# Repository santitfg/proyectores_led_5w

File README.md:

# redo
en el 74hc595 el pin 10 (rst ) si o si a vcc
y el pin 13 output enable va a gng si o si 

### Conector 1 — entrada de datos serie (SER)

Chip: 74HC595 (registro de desplazamiento serie-in / paralelo-out). Molex 5 pines.

| Pin | Color | Señal | GPIO ESP32 | GPIO ESP32-S3 | Descripción |
|-----|-------|-------|------------|---------------|-------------|
| 1   | ⚫ Negro  | GND   | —          | —             | Tierra |
| 2   | ⚪ Blanco | SRCLK / CP | `gpio23`   | `gpio18`      | Shift Clock (SH_CP, pin 11) / SPI2 SCLK |
| 3   | 🟢 Verde  | RCLK / PL | `gpio22`   | `gpio10`      | Register Clock / Latch (ST_CP, pin 12) |
| 4   | 🩶 Gris   | SER  / DS | `gpio2`    | `gpio4`       | Serial data in (DS, pin 14) / SPI2 MOSI |
| 5   | 🔴 Rojo   | VCC   | —          | —             | Alimentación |

### Conector 2 — salida en cascada (Q7)

Conector para encadenar el `SER` (pin 14) del siguiente 74HC595 a la salida en cascada `Q7'` (pin 9) de este.

| Pin | Color | Señal | GPIO ESP32 | GPIO ESP32-S3 | Descripción |
|-----|-------|-------|------------|---------------|-------------|
| 1   | ⚫ Negro  | GND   | —          | —             | Tierra |
| 2   | ⚪ Blanco | SRCLK  / CP| `gpio23`   | `gpio18`      | Shift Clock (SH_CP, pin 11) / SPI2 SCLK |
| 3   | 🟢 Verde  | RCLK  / PL | `gpio22`   | `gpio10`      | Register Clock / Latch (ST_CP, pin 12) |
| 4   | 🩶 Gris   | Q7   | `gpio35`   | `gpio5`       | Salida en cascada (Q7', pin 9) hacia el `SER` del siguiente 74HC595 |
| 5   | 🔴 Rojo   | VCC   | —          | —             | Alimentación |

estoy controlando con el 74hc595 la matriz desde las siguientes filas y columnas:
Q0 ... Q3 se conectan a los 2n2222 controlanto el gate de IRF9630
Q4 ... Q7 se conectan directo al gate IRLZ44N

# revision de laburo

PCB

IRF9630 high side y esta a up down en gate
IRLZ44N	low side y esta a pull down en gate

————

revision en protoboard 5v y señales activas de irlz44n y 2n2222 a 3.3:
IRLZ44N
gate ( pin 1) 10k a pull Down 1k a señal (vcc activa el paso de corriente)
drain ( pin 2) a gnd-terminal
source (pin 3) a GND

IRF9630
gate ( pin 1) 10k a pull up 1k a señal (gnd activa el paso de corriente)(2n2222)
drain ( pin 2) a Vout-terminal
source (pin 3) a VIN

2n2222 ( funcionamiento real es emisor a gnd y colector lado vcc)
emisor (pin 1) a GND
base (pin 2) señal ic ( via 1k Resi)
colector (pin 3) ( señal hacia irf9630 via 1k resi) vcc activa el paso de corriente)x

TODO: arreglar kicad corrigiendo los elementos mencionados (inverti pista VIN x Vout-terminal)

Fallas en el circuito funciona la mitad de puntos en modo damero
O X O X
X O X O 
O X O X
X O X O

Nomenclar correstamente las columnas y filas 
pero los v y gnd en los mismos no todos fallan de la misma manera
1: 2: 3: 4: 

Filas
q0 (pin 15) : IRF9630 1
q1 (pin 1) : IRF9630 2
q2 (pin 2) : IRF9630 3
q3 (pin 3) : IRF9630 4

Columnas
q4 (pin 4) : IRLZ44N 1
q5 (pin 5) : IRLZ44N 2
q6 (pin 6) : IRLZ44N 3
q7 (pin 7) : IRLZ44N 4

.   q4  q3  q2  q1
q3  4   3   2   1
q2  8   7   6   5
q1  12  11  10  9
q0  16  15  14  13     

funciona raro al enviar 0xFF se apagan las salidas y al 0x00 se prenden

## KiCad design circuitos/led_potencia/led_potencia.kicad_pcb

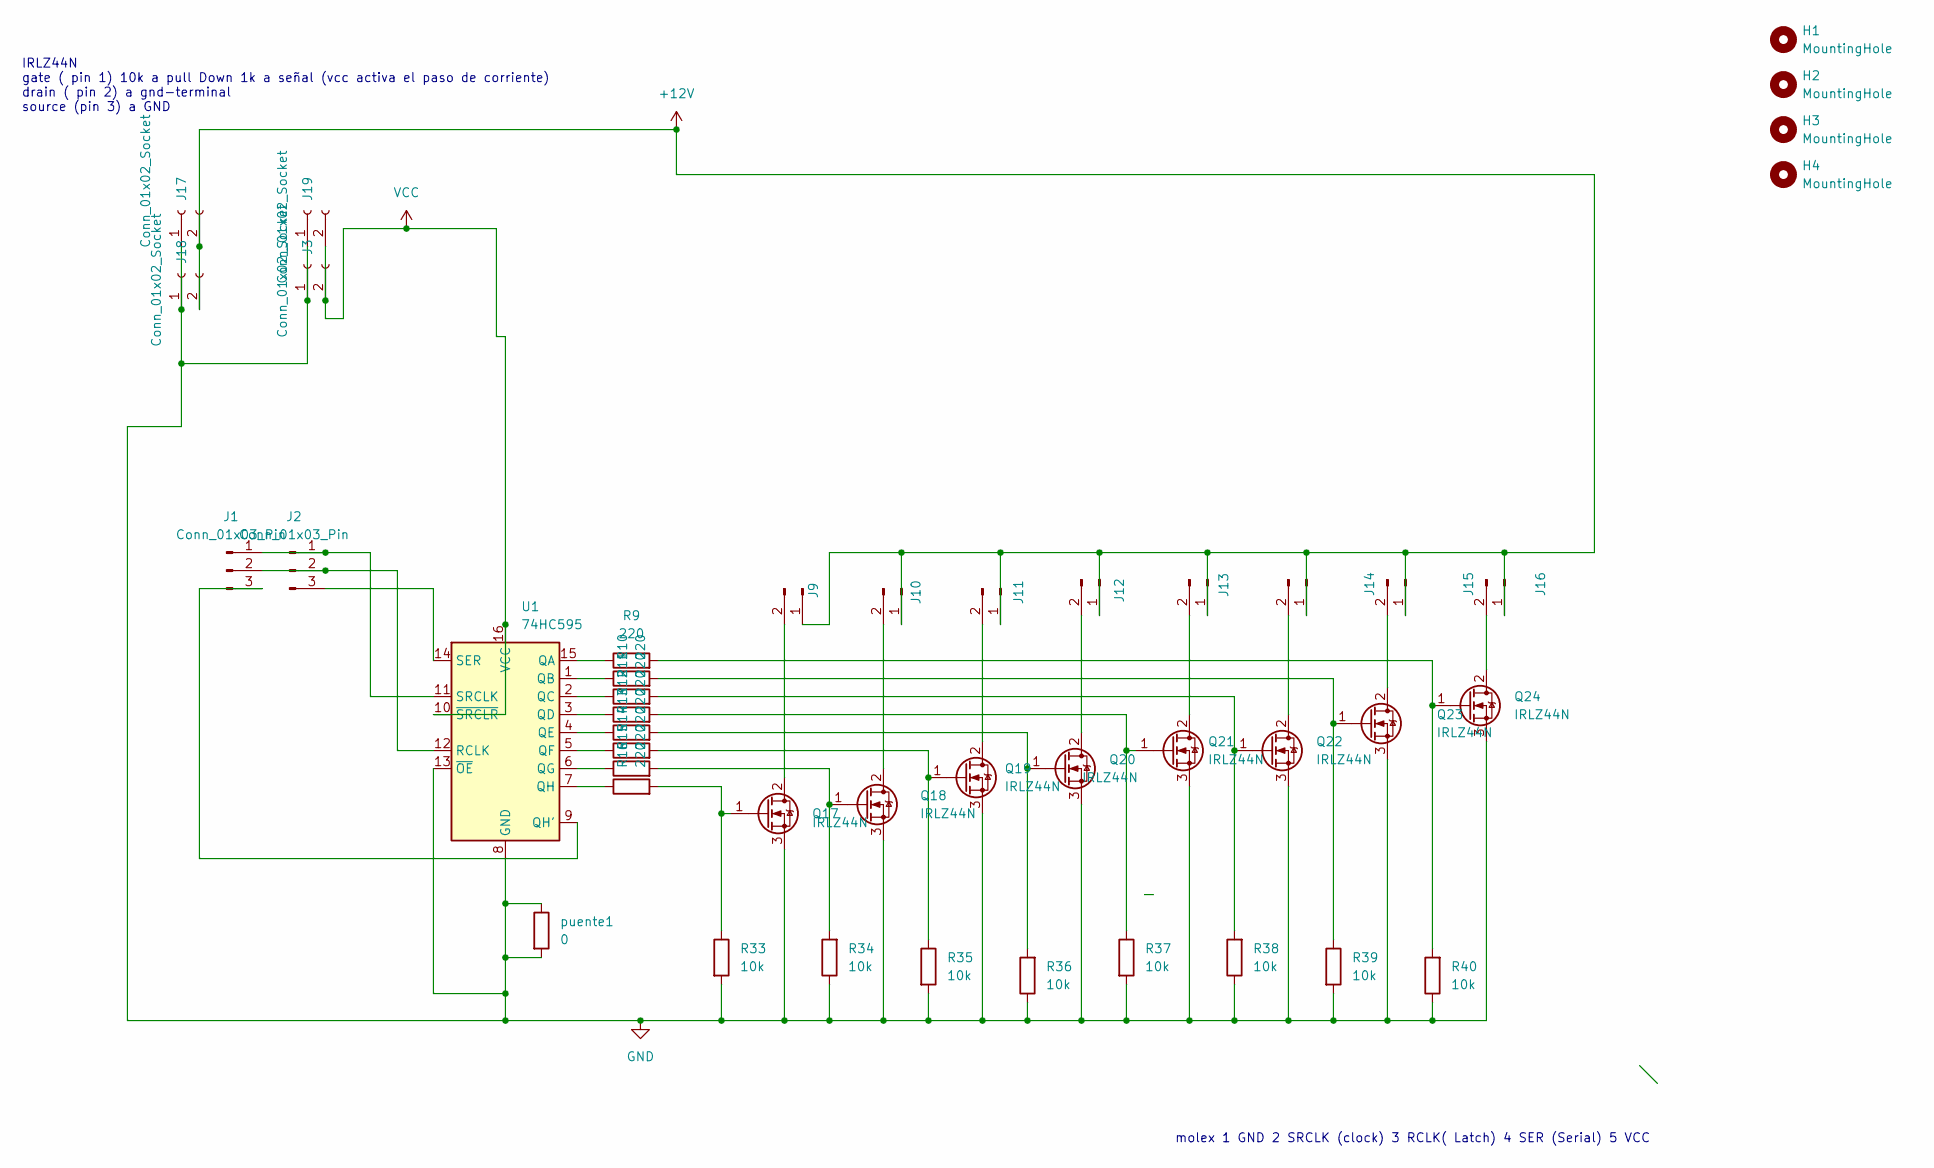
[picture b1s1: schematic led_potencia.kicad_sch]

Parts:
H1, H2, H3, H4: MountingHole; MountingHole_2.2mm_M2_DIN965_Pad
J1, J2: Conn_01x03_Pin; Molex_KK-254_AE-6410-03A_1x03_P2.54mm_Vertical
J3, J17, J18, J19: Conn_01x02_Socket; Molex_KK-254_AE-6410-02A_1x02_P2.54mm_Vertical
J9, J10, J11, J12, J13, J14, J15, J16: Conn_01x02_Pin; Molex_KK-254_AE-6410-02A_1x02_P2.54mm_Vertical
Q17, Q18, Q19, Q20, Q21, Q22, Q23, Q24: IRLZ44N; TO-220-3_Vertical
R9, R10, R11, R12, R13, R14, R15, R16: 220; R_Axial_DIN0204_L3.6mm_D1.6mm_P7.62mm_Horizontal
R33, R34, R35, R36, R37, R38, R39, R40: 10k; R_Axial_DIN0204_L3.6mm_D1.6mm_P7.62mm_Horizontal
U1: 74HC595; DIP-16_W7.62mm_Socket_LongPads
puente1: 0; R_Axial_DIN0204_L3.6mm_D1.6mm_P7.62mm_Horizontal

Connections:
+12V: J9.1, J10.1, J11.1, J12.1, J13.1, J14.1, J15.1, J16.1, J17.2, J18.2
GND: J3.1, J17.1, J18.1, J19.1, Q17.3 (S), Q18.3 (S), Q19.3 (S), Q20.3 (S), Q21.3 (S), Q22.3 (S), Q23.3 (S), Q24.3 (S), R33.2, R34.1, R35.2, R36.1, R37.2, R38.1, R39.2, R40.1, U1.8 (GND), U1.13 (~OE), puente1.1, puente1.2
unnamed: J1.1, J2.1, U1.11 (SRCLK)
unnamed: J1.2, J2.2, U1.12 (RCLK)
unnamed: J1.3, U1.9 (QH')
unnamed: J2.3, U1.14 (SER)
unnamed: J9.2, Q17.2 (D)
unnamed: J10.2, Q18.2 (D)
unnamed: J11.2, Q19.2 (D)
unnamed: J12.2, Q20.2 (D)
unnamed: J13.2, Q21.2 (D)
unnamed: J14.2, Q22.2 (D)
unnamed: J15.2, Q23.2 (D)
unnamed: J16.2, Q24.2 (D)
unnamed: Q17.1 (G), R16.2, R33.1
unnamed: Q18.1 (G), R15.2, R34.2
unnamed: Q19.1 (G), R14.2, R35.1
unnamed: Q20.1 (G), R13.2, R36.2
unnamed: Q21.1 (G), R12.2, R37.1
unnamed: Q22.1 (G), R11.2, R38.2
unnamed: Q23.1 (G), R10.2, R39.1
unnamed: Q24.1 (G), R9.2, R40.2
unnamed: R9.1, U1.15 (QA)
unnamed: R10.1, U1.1 (QB)
unnamed: R11.1, U1.2 (QC)
unnamed: R12.1, U1.3 (QD)
unnamed: R13.1, U1.4 (QE)
unnamed: R14.1, U1.5 (QF)
unnamed: R15.1, U1.6 (QG)
unnamed: R16.1, U1.7 (QH)
VCC: J3.2, J19.2, U1.10 (~SRCLR), U1.16 (VCC)

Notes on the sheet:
IRLZ44N gate ( pin 1) 10k a pull Down 1k a señal (vcc activa el paso de corriente) drain ( pin 2) a gnd-terminal source (pin 3) a GND
molex 1 GND 2 SRCLK (clock) 3 RCLK( Latch) 4 SER (Serial) 5 VCC

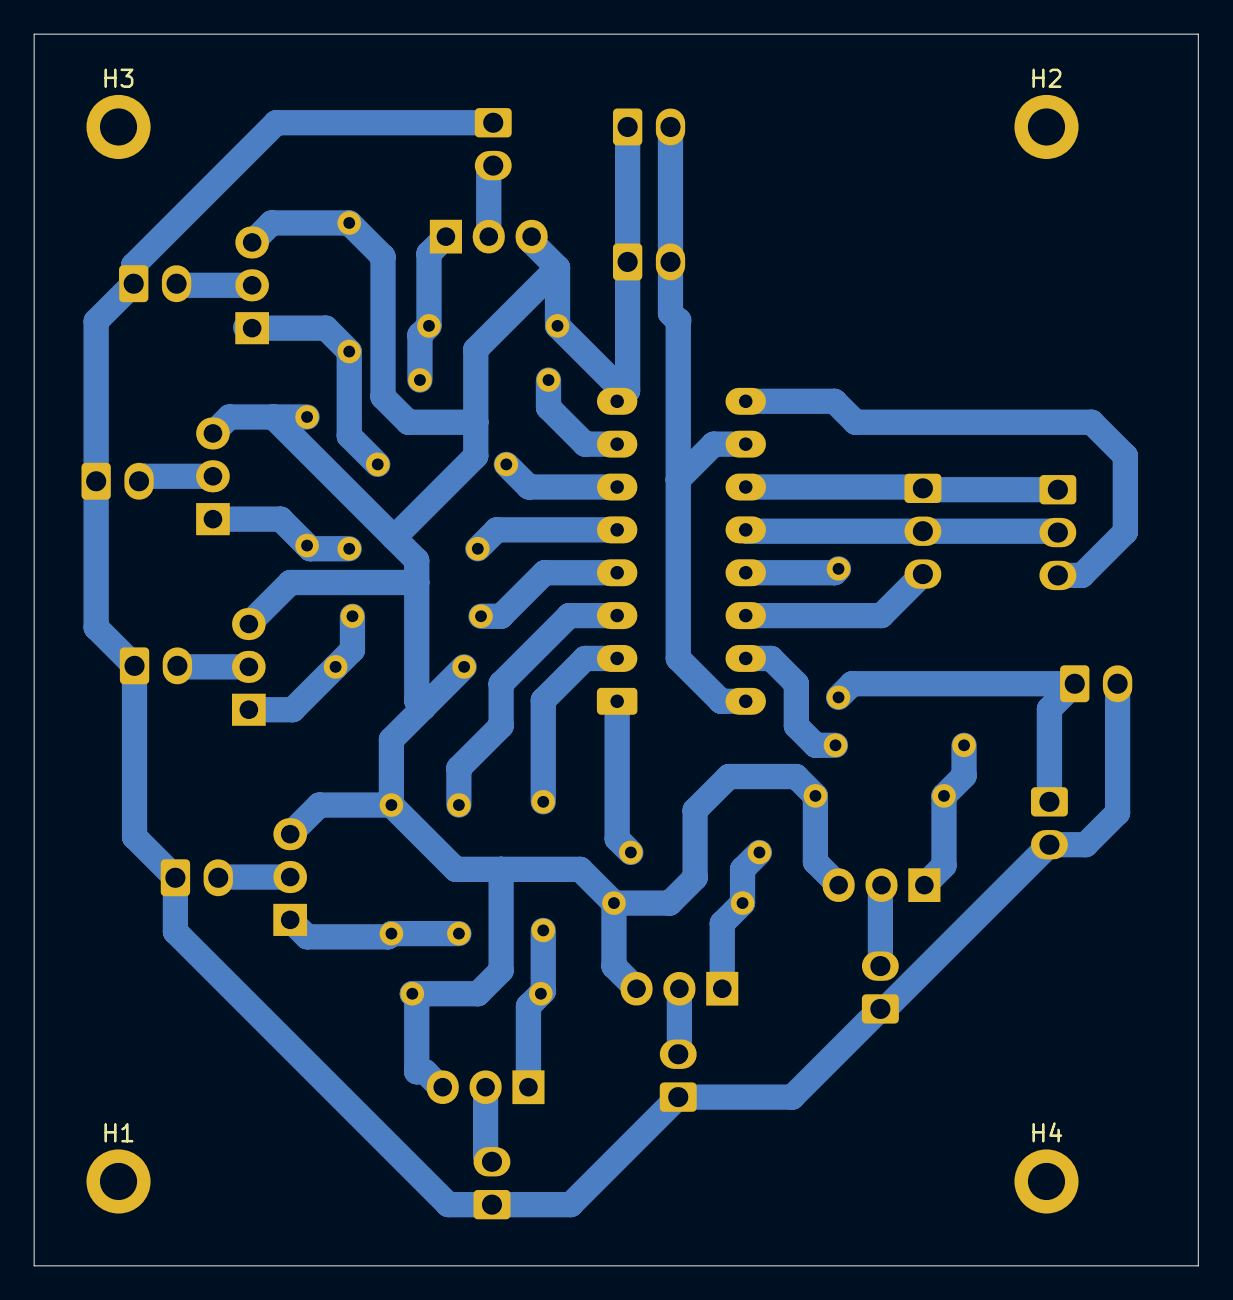
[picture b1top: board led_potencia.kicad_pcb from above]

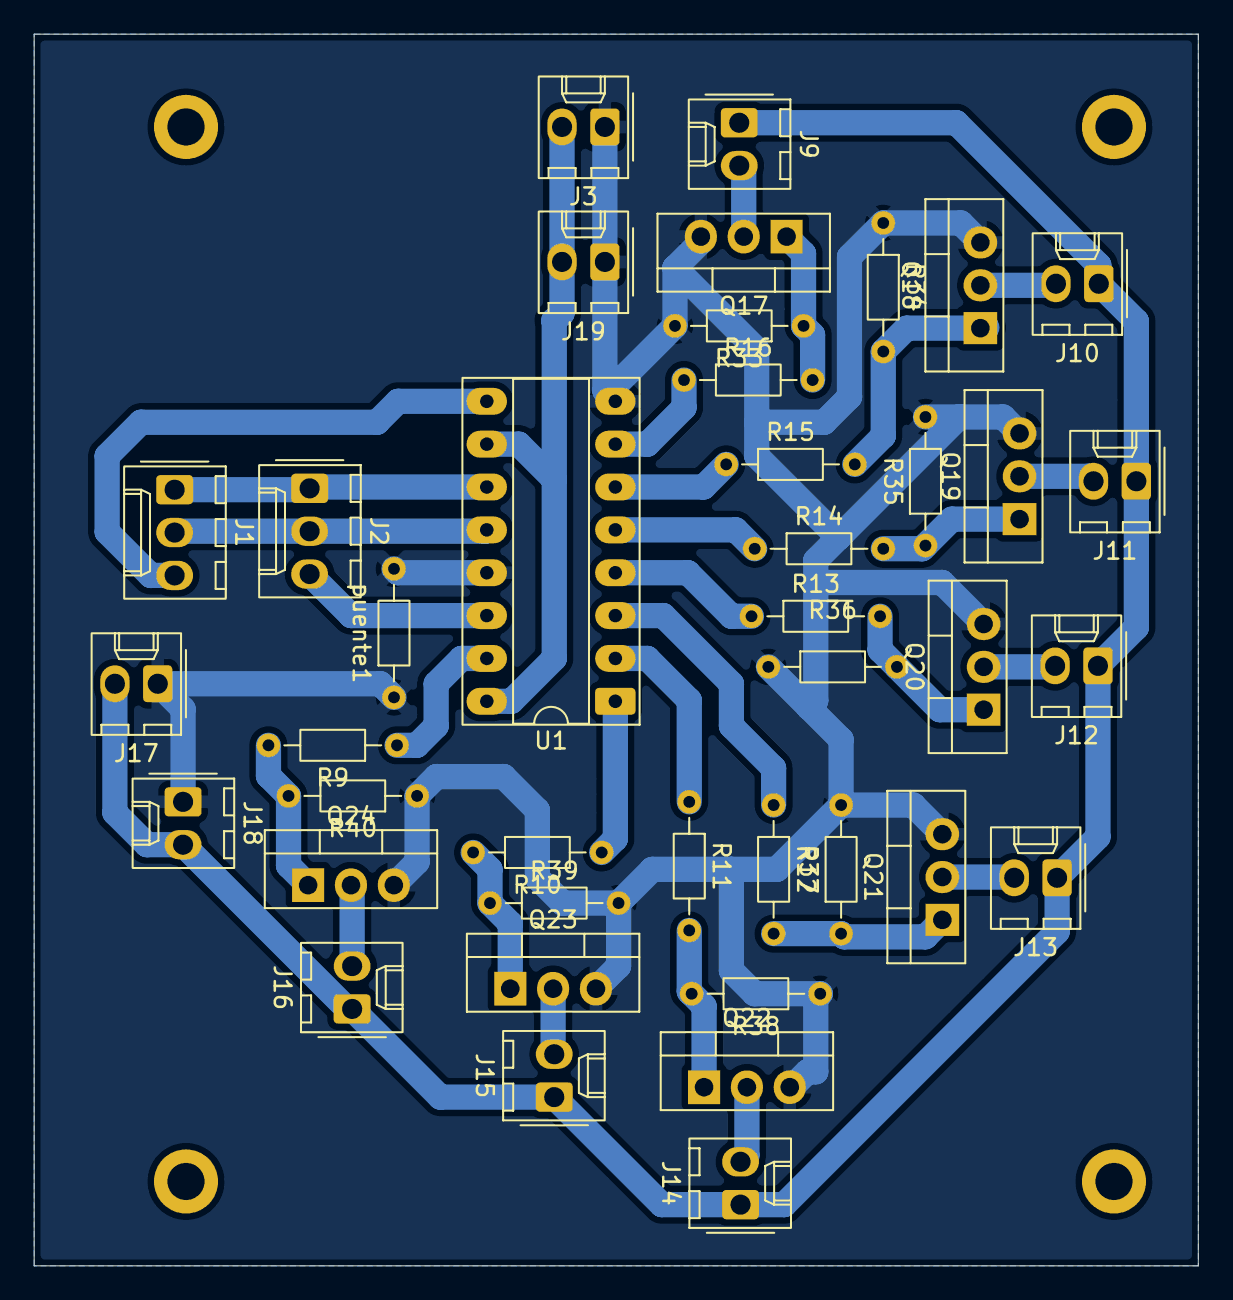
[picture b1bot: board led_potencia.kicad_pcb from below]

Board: 2 copper layers, 69.0 x 73.0 mm, 44 parts (40 on the bottom side), 31 nets.

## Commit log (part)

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2026-06-10 sketch verde iniciando
2026-06-10 sumando demos funconales
2026-06-11 funcional pero descontrolador
2026-06-16 circuito wip
2026-06-16 mejorando array
2026-06-26 logica funcionan pasando a pcb
2026-06-28 sumando cambios
2026-06-29 armando grilla PCB
2026-06-29 circuito pre finalizado, retestear en proto e imprimir
2026-06-30 in out añadidos
2026-06-30 variante de ruteo v2 contrastar?
2026-06-30 obse nomai v3 de ruteo (podria achicarse mucho mas pero no es sano
